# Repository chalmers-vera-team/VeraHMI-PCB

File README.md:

[Interactive BOM](http://htmlpreview.github.io/?https://github.com/chalmers-vera-team/VeraHMI-PCB/blob/master/bom/ibom.html)

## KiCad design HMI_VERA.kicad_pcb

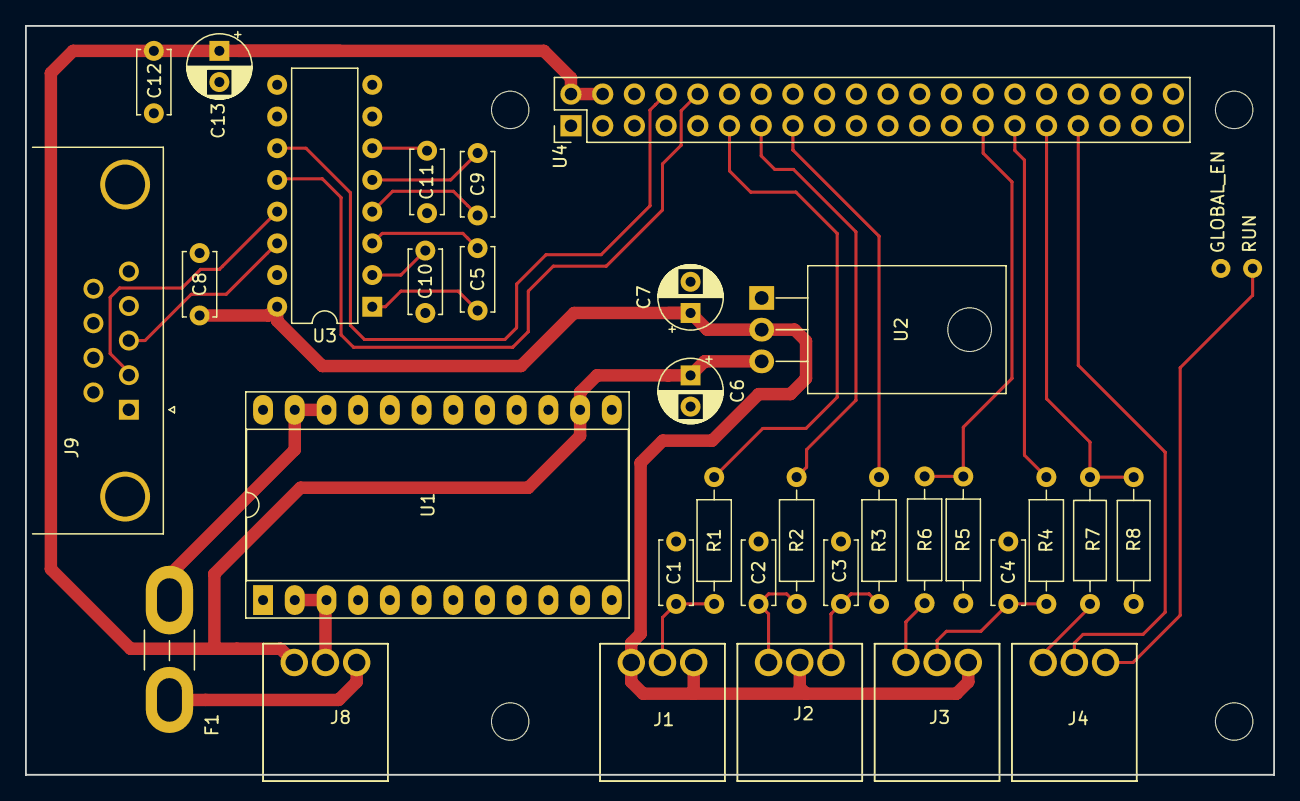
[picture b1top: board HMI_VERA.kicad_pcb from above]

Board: 2 copper layers, 100.0 x 60.0 mm, 32 parts (0 on the bottom side), 30 nets.

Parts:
C1, C2, C3, C4: 10n; C_Disc_D5.0mm_W2.5mm_P5.00mm
C5, C8, C9, C10, C11, C12: 100n; C_Disc_D5.0mm_W2.5mm_P5.00mm
C6, C7: 10u; CP_Radial_D5.0mm_P2.50mm
C13: 47u; CP_Radial_D5.0mm_P2.50mm
F1: 2A; BladeFuse-Mini
J1, J2, J3, J4, J8: Conn_01x03; 205-15EDGRC-2.5-03P
J9: DB9_Female; DSUB-9_Female_Horizontal_P2.77x2.84mm_EdgePinOffset4.94mm_H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
R1, R2, R3, R4: 10k; R_Axial_DIN0207_L6.3mm_D2.5mm_P10.16mm_Horizontal
R5: 6k2; R_Axial_DIN0207_L6.3mm_D2.5mm_P10.16mm_Horizontal
R6: 3k3; R_Axial_DIN0207_L6.3mm_D2.5mm_P10.16mm_Horizontal
R7: 300k; R_Axial_DIN0207_L6.3mm_D2.5mm_P10.16mm_Horizontal
R8: 100k; R_Axial_DIN0207_L6.3mm_D2.5mm_P10.16mm_Horizontal
U1: THD10-1211N; DIP-24_W15.24mm_Socket_LongPads
U2: LM1117-3.3; TO-220-3_Horizontal_TabDown
U3: MAX3232; DIP-16_W7.62mm
U4: RPI_3B+_Pinout_With_RUN; RPI_3B+_withRun

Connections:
+3V3: C7.1, C8.2, J1.1, J1.3, J2.2, J3.3, U2.2, U3.16
+5V: C6.1, C12.1, C13.1, J8.1, U1.14, U2.3, U4.2, U4.4
+12V: J4.1, R7.2
+BATT: F1.1, U1.22, U1.23
GND: C1.2, C2.2, C3.2, C4.2, C6.2, C7.2, C8.1, C10.1, C11.1, C12.2, C13.2, J9.5, R5.2, R8.2, U1.16, U2.1, U3.15, U4.6, U4.9, U4.14, U4.20, U4.25, U4.30, U4.34, U4.39
unnamed: C1.1, J1.2, R1.2
unnamed: C2.1, J2.1, R2.2
unnamed: C3.1, J2.3, R3.2
unnamed: C4.1, J3.2, R4.2
unnamed: C5.1, U3.1
unnamed: C5.2, U3.3
unnamed: C9.1, U3.4
unnamed: C9.2, U3.5
unnamed: C10.2, U3.2
unnamed: C11.2, U3.6
unnamed: F1.2, J8.3
unnamed: J4.2, U4.33
unnamed: J8.2, U1.2, U1.3
unnamed: R1.1, U4.11
unnamed: R2.1, U4.13
unnamed: R3.1, U4.15
unnamed: R4.1, U4.29
unnamed: R5.1, R6.2, U4.27
unnamed: R7.1, R8.1, U4.31
RUN: J4.3, U4.41
RX: U3.12, U4.10
RXD: J9.2, U3.13
SpeedOmeter: J3.1, R6.1
TX: U3.11, U4.8
TXD: J9.3, U3.14

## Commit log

2019-05-27 Add Gerbers to Gitignore.
2019-05-27 Add drill files to Gitignore.
2019-05-27 Upload rev 1.
2019-05-27 Solve library import error. Upload .lib.
2019-05-27 Solve derived library errors.
2019-05-27 Change to RPi B3+ footprint. PCB currently broken.
2019-05-31 Correct Rpi footprint. Add Rpi mcad model.
2019-05-31 Add batt volt div to schematic.
2019-05-31 Add 12V fuse to schematic.
2019-05-31 Remove unused connectors.
2019-05-31 Rev 2 completed
2019-05-31 SVG hotfix
2019-05-31 Gerber gitignore fix
2019-06-02 Change voltage dividier input from BATT+ to 12V+.
2019-06-02 Save hotfix.
2019-06-02 Change mouting holes from Edge cuts to footprint.
2019-06-08 Add BOM and assign component product codes.
2019-06-08 Add link to interactive BOM html in README
2019-06-24 Add board dimensions to drawing.
